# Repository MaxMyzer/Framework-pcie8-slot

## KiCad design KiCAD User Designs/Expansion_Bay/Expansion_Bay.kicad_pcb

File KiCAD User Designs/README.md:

# User Designs

Templates and User Designs for KiCAD

## Template
It is preloaded with the Framework Expansion Bay Interface, the Fan circuits, all technical drawings (User.Drawings, User.2, User.3), and two board outlines (normal in User.Eco2, 100m wide in User.Eco1)

## OCuLink Expansion Bay

<image src="OCuLink_Expansion_Bay/production/Image_Wide.png">

A card design for attaching external PCIe Gen 4 x8 Devices via dual OCuLink 4i connectors. Uses DisplayPort and all 8 PCIe data lanes on a 4 layer board.

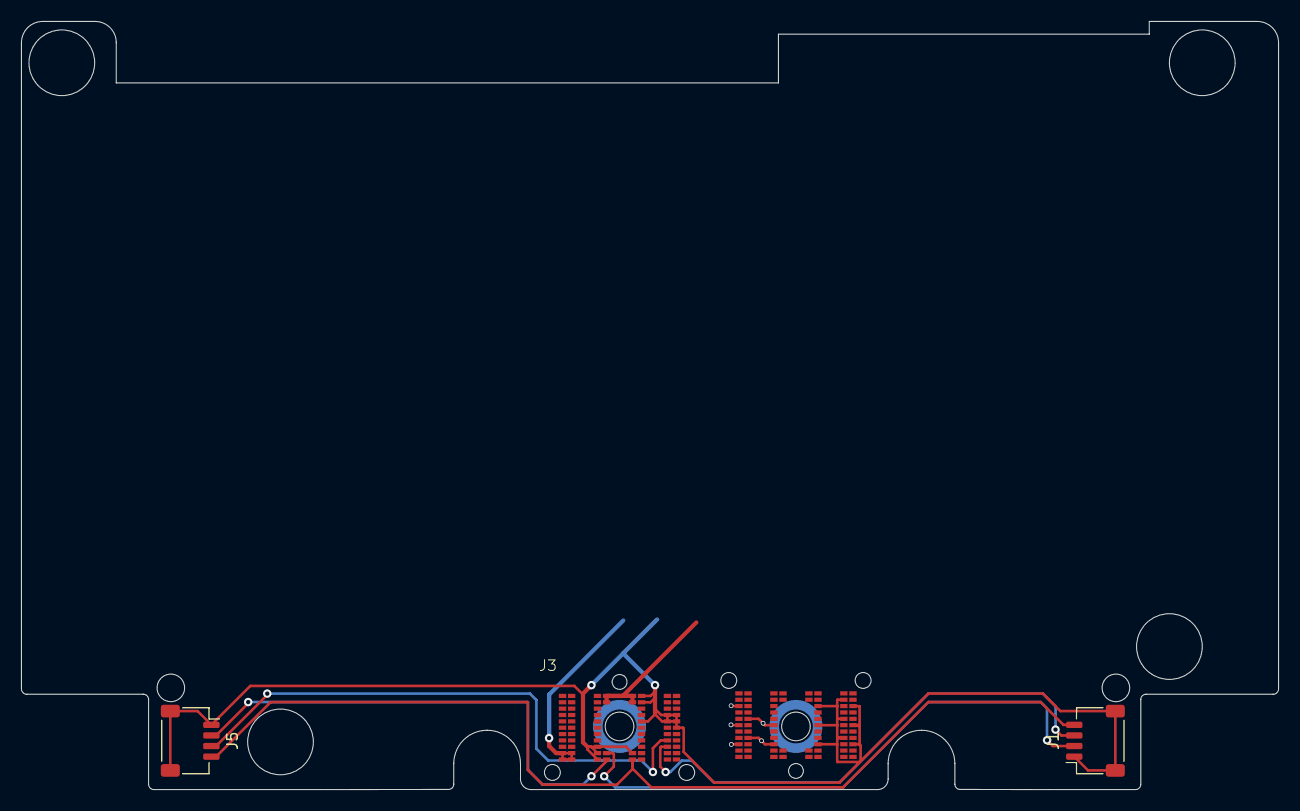
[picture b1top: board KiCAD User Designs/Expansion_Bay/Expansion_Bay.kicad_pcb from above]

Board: 4 copper layers, 118.7 x 72.5 mm, 3 parts (0 on the bottom side), 13 nets.

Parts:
J1: FAN1; JST_SH_SM04B-SRSS-TB_1x04-1MP_P1.00mm_Horizontal
J3: FW_EBI; 2x74P FXBeam
J5: FAN0; JST_SH_SM04B-SRSS-TB_1x04-1MP_P1.00mm_Horizontal

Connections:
/3.3V: J3.PA4 (3V3_ALW), J3.PA5 (3V3_ALW), J3.PB4 (3V3_ALW), J3.PB5 (3V3_ALW)
/5V: J3.PK7 (5V_ALW), J3.PK8 (5V_ALW), J3.PL7 (5V_ALW), J3.PL8 (5V_ALW)
/12V_FAN: J1.4, J3.PL4 (12V_FAN), J5.4
/FAN0_PWM: J3.PL5 (Fan0_PWM), J5.2
/FAN0_SPEED: J3.PH2 (Fan0_SPEED), J5.3
/FAN1_PWM: J1.2, J3.PK5 (Fan1_PWM)
/FAN1_SPEED: J1.3, J3.PJ2 (Fan1_SPEED)
GND: J1.1, J1.MP (Shield), J3.PA3 (GND), J3.PB3 (GND), J3.PD1 (GND), J3.PD2 (GND), J3.PE1 (GND), J3.PE2 (GND), J3.PE3 (GND), J3.PF1 (GND), J3.PJ6 (GND), J3.PK4 (GND), J3.PK6 (GND), J3.PL6 (GND), J5.1, J5.MP (Shield)
unnamed: J3.PA6 (GND), J3.PB6 (GND), J3.PC6 (GND), J3.PD6 (GND), J3.PE6 (GND), J3.PF6 (GND), J3.PG6 (GND), J3.PH6 (GND), J3.PH7 (GND), J3.PH8 (GND), J3.PJ7 (GND), J3.PJ8 (GND)
unnamed: J3.PH3 (GND), J3.PL3 (GND)
unnamed: J3.SB2 (GND), J3.SB7 (GND), J3.SC1 (GND), J3.SC3 (GND), J3.SC6 (GND), J3.SC8 (GND), J3.SE2 (GND), J3.SE7 (GND), J3.SF1 (GND), J3.SF3 (GND), J3.SF6 (GND), J3.SF8 (GND), J3.SH2 (GND), J3.SH7 (GND), J3.SJ1 (GND), J3.SJ3 (GND), J3.SJ6 (GND), J3.SJ8 (GND)
unnamed: J3.PA7 (VSYS_GPU), J3.PA8 (VSYS_GPU), J3.PB7 (VSYS_GPU), J3.PB8 (VSYS_GPU), J3.PC7 (VSYS_GPU), J3.PC8 (VSYS_GPU), J3.PD7 (VSYS_GPU), J3.PD8 (VSYS_GPU), J3.PE7 (VSYS_GPU), J3.PE8 (VSYS_GPU), J3.PF7 (VSYS_GPU), J3.PF8 (VSYS_GPU), J3.PG7 (VSYS_GPU), J3.PG8 (VSYS_GPU)
VADP_GPU: J3.PA1 (VADP_GPU), J3.PA2 (VADP_GPU), J3.PB1 (VADP_GPU), J3.PB2 (VADP_GPU), J3.PC1 (VADP_GPU), J3.PC2 (VADP_GPU)

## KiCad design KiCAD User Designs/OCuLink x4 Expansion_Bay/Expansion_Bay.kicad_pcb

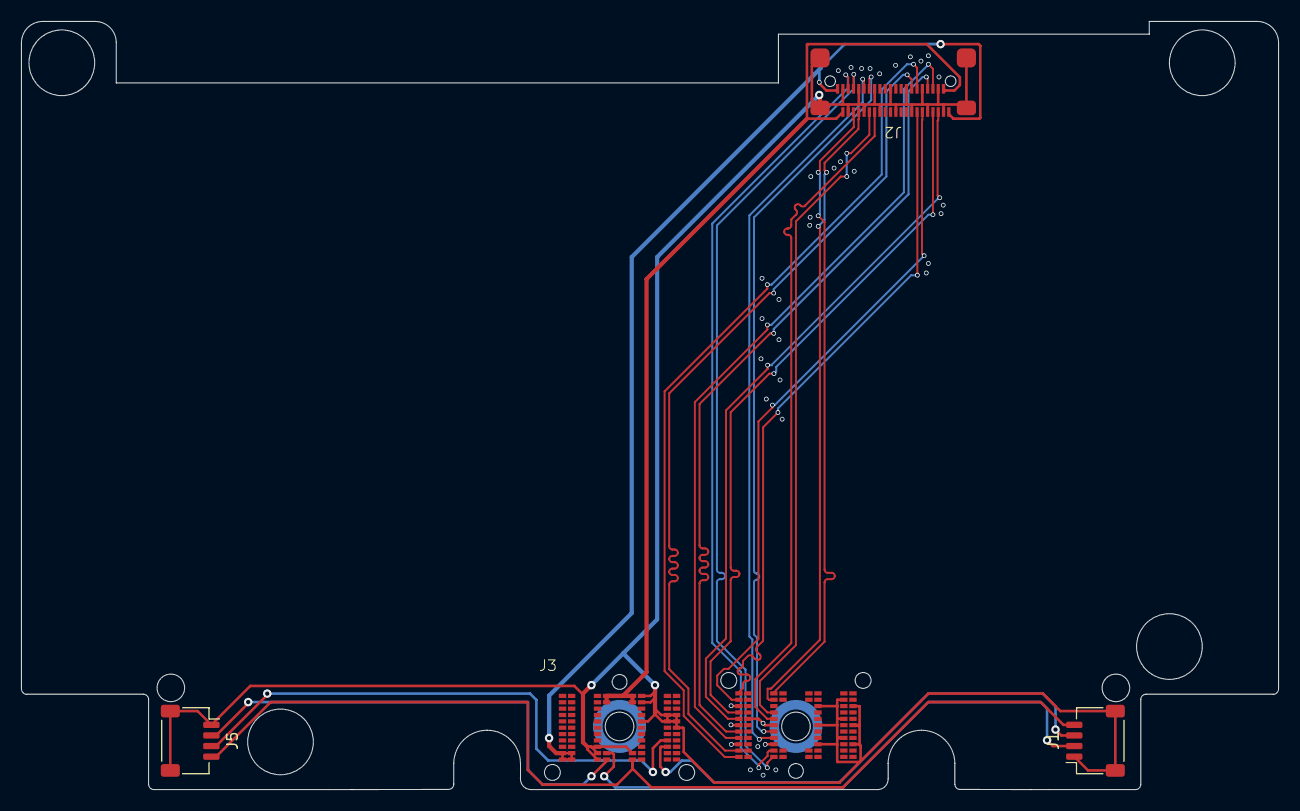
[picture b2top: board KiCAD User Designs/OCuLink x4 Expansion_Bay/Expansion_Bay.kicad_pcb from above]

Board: 4 copper layers, 118.7 x 72.5 mm, 4 parts (0 on the bottom side), 28 nets.

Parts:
J1: FAN1; JST_SH_SM04B-SRSS-TB_1x04-1MP_P1.00mm_Horizontal
J2: G14A421X11X1XHR
J3: FW_EBI; 2x74P FXBeam
J5: FAN0; JST_SH_SM04B-SRSS-TB_1x04-1MP_P1.00mm_Horizontal

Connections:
/3.3V: J2.A1 (3.3V_RX), J2.B21 (3.3V_TX), J3.PA4 (3V3_ALW), J3.PA5 (3V3_ALW), J3.PB4 (3V3_ALW), J3.PB5 (3V3_ALW)
/5V: J2.A21 (5V), J2.B1 (5V), J3.PK7 (5V_ALW), J3.PK8 (5V_ALW), J3.PL7 (5V_ALW), J3.PL8 (5V_ALW)
/12V_FAN: J1.4, J3.PL4 (12V_FAN), J5.4
/FAN0_PWM: J3.PL5 (Fan0_PWM), J5.2
/FAN0_SPEED: J3.PH2 (Fan0_SPEED), J5.3
/FAN1_PWM: J1.2, J3.PK5 (Fan1_PWM)
/FAN1_SPEED: J1.3, J3.PJ2 (Fan1_SPEED)
/PEX_RX0_N: J2.B4 (PEX_TX0N), J3.SD8 (PEX_RX0N)
/PEX_RX0_P: J2.B3 (PEX_TX0P), J3.SE8 (PEX_RX0P)
/PEX_RX1_N: J2.B7 (PEX_TX1N), J3.SA8 (PEX_RX1N)
/PEX_RX1_P: J2.B6 (PEX_TX1P), J3.SB8 (PEX_RX1P)
/PEX_RX2_N: J2.B16 (PEX_TX2N), J3.SD6 (PEX_RX2N)
/PEX_RX2_P: J2.B15 (PEX_TX2P), J3.SE6 (PEX_RX2P)
/PEX_RX3_N: J2.B19 (PEX_TX3N), J3.SA6 (PEX_RX3N)
/PEX_RX3_P: J2.B18 (PEX_TX3P), J3.SB6 (PEX_RX3P)
/PEX_TX0_N: J2.A4 (PEX_RX0N), J3.SG8 (PEX_TX0N)
/PEX_TX0_P: J2.A3 (PEX_RX0P), J3.SH8 (PEX_TX0P)
/PEX_TX1_N: J2.A7 (PEX_RX1N), J3.SK8 (PEX_TX1N)
/PEX_TX1_P: J2.A6 (PEX_RX1P), J3.SL8 (PEX_TX1P)
/PEX_TX2_N: J2.A16 (PEX_RX2N), J3.SH6 (PEX_TX2N)
/PEX_TX2_P: J2.A15 (PEX_RX2P), J3.SG6 (PEX_TX2P)
/PEX_TX3_N: J2.A19 (PEX_RX3N), J3.SK6 (PEX_TX3N)
/PEX_TX3_P: J2.A18 (PEX_RX3P), J3.SL6 (PEX_TX3P)
GND: J1.1, J1.MP (Shield), J2.A2 (GND), J2.A5 (GND), J2.A8 (GND), J2.A11 (GND), J2.A14 (GND), J2.A17 (GND), J2.A20 (GND), J2.B2 (GND), J2.B5 (GND), J2.B8 (GND), J2.B11 (GND), J2.B14 (GND), J2.B17 (GND), J2.B20 (GND), J2.MP (Case), J3.PA3 (GND), J3.PB3 (GND), J3.PD1 (GND), J3.PD2 (GND), J3.PE1 (GND), J3.PE2 (GND), J3.PE3 (GND), J3.PF1 (GND), J3.PJ6 (GND), J3.PK4 (GND), J3.PK6 (GND), J3.PL6 (GND), J3.SB2 (GND), J3.SB7 (GND), J3.SC1 (GND), J3.SC3 (GND), J3.SC6 (GND), J3.SC8 (GND), J3.SE2 (GND), J3.SE7 (GND), J3.SF1 (GND), J3.SF3 (GND), J3.SF6 (GND), J3.SF8 (GND), J3.SH2 (GND), J3.SH7 (GND), J3.SJ1 (GND), J3.SJ3 (GND), J3.SJ6 (GND), J3.SJ8 (GND), J5.1, J5.MP (Shield)
unnamed: J3.PA6 (GND), J3.PB6 (GND), J3.PC6 (GND), J3.PD6 (GND), J3.PE6 (GND), J3.PF6 (GND), J3.PG6 (GND), J3.PH6 (GND), J3.PH7 (GND), J3.PH8 (GND), J3.PJ7 (GND), J3.PJ8 (GND)
unnamed: J3.PH3 (GND), J3.PL3 (GND)
unnamed: J3.PA7 (VSYS_GPU), J3.PA8 (VSYS_GPU), J3.PB7 (VSYS_GPU), J3.PB8 (VSYS_GPU), J3.PC7 (VSYS_GPU), J3.PC8 (VSYS_GPU), J3.PD7 (VSYS_GPU), J3.PD8 (VSYS_GPU), J3.PE7 (VSYS_GPU), J3.PE8 (VSYS_GPU), J3.PF7 (VSYS_GPU), J3.PF8 (VSYS_GPU), J3.PG7 (VSYS_GPU), J3.PG8 (VSYS_GPU)
VADP_GPU: J3.PA1 (VADP_GPU), J3.PA2 (VADP_GPU), J3.PB1 (VADP_GPU), J3.PB2 (VADP_GPU), J3.PC1 (VADP_GPU), J3.PC2 (VADP_GPU)

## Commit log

2023-07-31 OCuLink x4 Expansion Bay & Templates
2023-08-08 Updated Board, Dual OCuLink 4i + DP
    New board specifications, new template
    Proper schematic and routing for dual 4i + DP in ports
    Both full size and 100mm boards
2024-04-16 remove non-template files
2024-04-19 Mess everything up
